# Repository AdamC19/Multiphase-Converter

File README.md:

# Multiphase Forward Converter
This repo contains the hardware source files for my digitally controlled multiphase isolated 1000W forward
converter. (firmware source code repo is
[here](https://github.com/AdamC19/Multiphase-Converter-FW).) This is a work in progress

## Update December 2020
First prototype has been built up, initial testing is promising! See more [here](http://acordingley.us/multiphase-converter/).

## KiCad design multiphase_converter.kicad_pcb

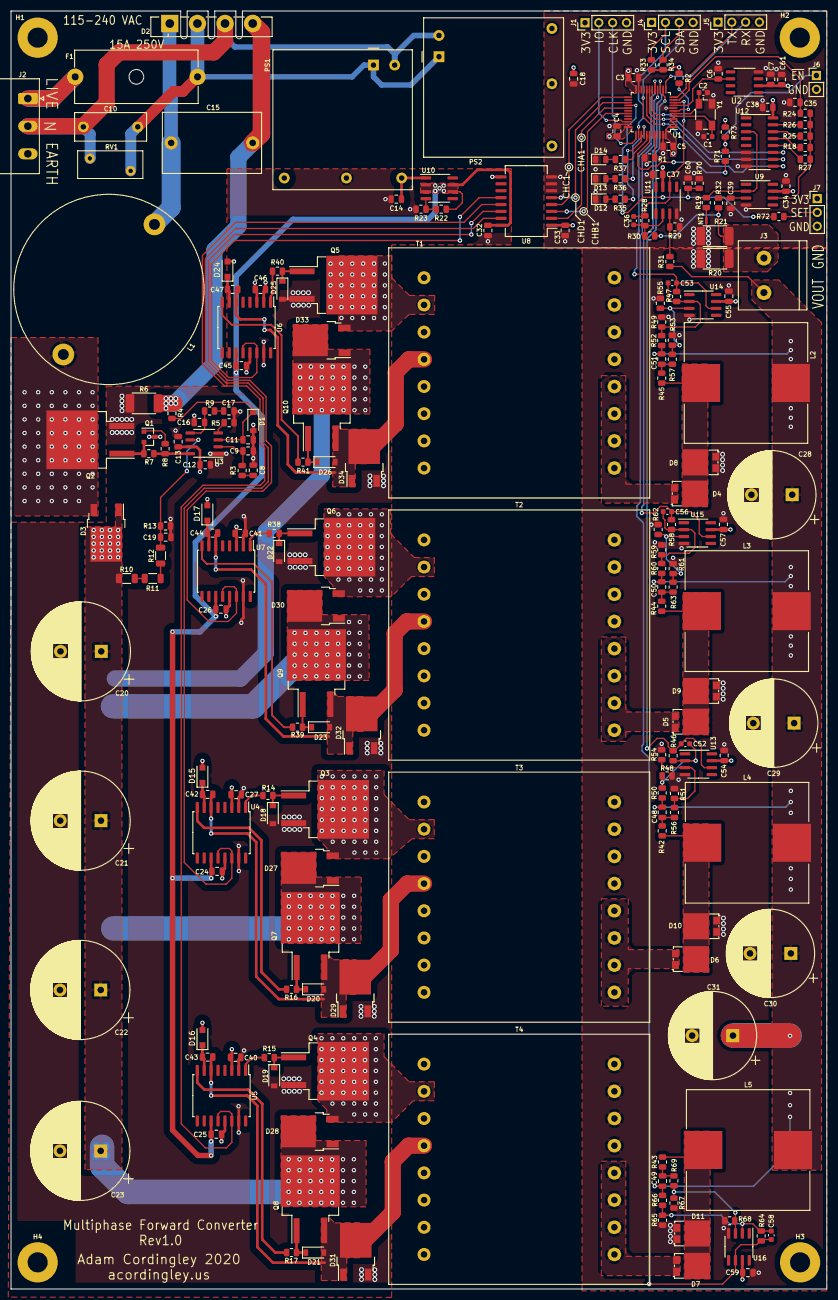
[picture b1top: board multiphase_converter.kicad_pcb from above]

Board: 4 copper layers, 150.0 x 235.0 mm, 220 parts (0 on the bottom side), 123 nets.

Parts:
C1, C2: 18p; C_0603_1608Metric
C3, C4, C5, C7, C13, C24, C25, C26, C27, C32, C33, C34, C35, C37, C38, C40, C41, C42, C43, C44, C45, C46, C47, C48, C49, C50, C51, C54, C55, C57, C59, C60: 0.1u; C_0805_2012Metric
C6, C12, C61: 1u; C_0805_2012Metric
C8: DNP; C_0805_2012Metric
C9, C11: 1200p; C_0805_2012Metric
C10: 4700p; C_Rect_L13.0mm_W5.0mm_P10.00mm_FKS3_FKP3_MKS4
C14, C18: 10u; C_0805_2012Metric
C15: R463I347050N0M; C_Rect_L18.0mm_W11.0mm_P15.00mm_FKS3_FKP3
C16: 2.2u; C_0805_2012Metric
C17: 22u; C_0805_2012Metric
C19: 680p; C_0805_2012Metric
C20, C21, C22, C23: 220u; CP_Radial_D18.0mm_P7.50mm
C28, C29, C30, C31: UCS2C221MHD1TN; CP_Radial_D16.0mm_P7.50mm
C36, C52, C53, C56, C58: 6.8p; C_0603_1608Metric
C39: 0.01u; C_0805_2012Metric
D1: 1N4148W; D_SOD-123
D2: GBU2510-G; Diode_Bridge_Vishay_GBU
D3, D27, D28, D29, D30, D31, D32, D33, D34: C3D04060E; TO-252-2
D4, D5, D6, D7, D8, D9, D10, D11: FSV15100V; TO-277A
D12, D13, D14: LED; LED_0805_2012Metric
D15, D16, D17, D24: S1MFL; D_SOD-123F
D18, D19, D20, D21, D22, D23, D25, D26: 15V; D_SOD-123
F1: 0031.8201; Fuseholder_Cylinder-5x20mm_Schurter_0031_8201_Horizontal_Op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
H1, H2, H3, H4: #6; MountingHole_3.7mm_Pad
J1, J4, J5: Conn_01x04_Male; PinHeader_1x04_P2.54mm_Vertical
J2: 1923872; PhoenixContact_MSTBA_2,5_3-G-5,08_1x03_P5.08mm_Horizontal
J3: 1714955; Phoenix_MKDS_5_2-6,35
J6: Conn_01x02_Male; PinHeader_1x02_P2.54mm_Vertical
J7: Conn_01x03_Male; PinHeader_1x03_P2.54mm_Vertical
L1: 120u; Bourns_1140_121K
L2, L3, L4, L5: 74435583300; L_Wuerth_HCI-2212
NT1: Net-Tie_2; NetTie-2_SMD_Pad0.5mm
PS1: RAC05-12SK; Converter_ACDC_RECOM_RAC05-xxSK_THT
PS2: RAC05-3.3SK; Converter_ACDC_RECOM_RAC05-xxSK_THT
Q1: BC807; SOT-23
Q2: IPB60R060P7ATMA1; TO-263-2
Q3, Q4, Q5, Q6, Q7, Q8, Q9, Q10: Q_NMOS_GDS; TO-263-2
R1, R2, R8, R19, R24, R32: 1k; R_0805_2012Metric
R3: DNP; R_0805_2012Metric
R4: 220; R_0805_2012Metric
R5: 13.7k; R_0805_2012Metric
R6: 0.015; R_2512_Power
R7, R14, R15, R16, R17, R38, R39, R40, R41: 3.3; R_0805_2012Metric
R9: 4.7k; R_0805_2012Metric
R10, R11, R12: 330k; R_1206_3216Metric
R13: 14.3k; R_0805_2012Metric
R18: 1.5M; R_0805_2012Metric
R20, R21: 0.003; R_2512_Power
R22: 240; R_0805_2012Metric
R23: 720; R_0805_2012Metric
R25, R30, R31, R50, R52, R56, R57, R60, R63, R66, R69, R70: 200k; R_0805_2012Metric
R26, R71, R72: 100k; R_0805_2012Metric
R27: 50k; R_0805_2012Metric
R28, R29, R48, R49, R51, R53, R59, R61, R65, R67, R73: 10k; R_0805_2012Metric
R33, R34: 2.2k; R_0805_2012Metric
R35, R36, R37: 330; R_0805_2012Metric
R42, R43, R44, R45: 25k; R_0805_2012Metric
R46, R47, R54, R55, R58, R62, R64, R68: 2.4M; R_0805_2012Metric
RV1: MOV-10D391KTR; RV_Disc_D12mm_W5.1mm_P7.5mm
T1, T2, T3, T4: Wurth_760895751
U1: STM32F334C8Tx; LQFP-48_7x7mm_P0.5mm
U2: ADR45xx; SO-8_3.9x4.9mm_P1.27mm
U3: UCC28180; SO-8_3.9x4.9mm_P1.27mm
U4, U5, U6, U7: IR2113S; SOIC-16W_7.5x10.3mm_P1.27mm
U8: ADuM260N; SOIC-16W_7.5x12.8mm_P1.27mm
U9: AD8551; SOIC-8_3.9x4.9mm_P1.27mm
U10: LM317L_SO8; SOIC-8_3.9x4.9mm_P1.27mm
U11, U13, U14, U15, U16: TSV911IDT; SOIC-8_3.9x4.9mm_P1.27mm
U12: 74HC4051; SOIC-16_3.9x9.9mm_P1.27mm
Y1: ABM3B-16.000MHZ-B2-T; Crystal_SMD_Abracon_ABM3B-4Pin_5.0x3.2mm

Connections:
+3V3: C3.2, C4.2, C5.2, C7.1, C18.1, C33.1, C34.1, C37.1, C38.1, C54.1, C55.1, C57.1, C59.1, C61.2, J1.1, J4.1, J5.1, J7.1, PS2.5, R2.1, R33.1, R34.1, R73.1, U1.1, U1.24, U1.36, U1.48, U2.2, U8.1, U9.7, U11.7, U12.16, U13.7, U14.7, U15.7, U16.7
+5VA: C24.1, C25.1, C26.1, C32.1, C45.1, R22.1, U4.11, U5.11, U6.11, U7.11, U8.16, U10.2, U10.3, U10.6, U10.7
+12V: C12.2, C13.2, C14.1, C27.2, C40.2, C41.2, C46.2, D15.2, D16.2, D17.2, D24.2, PS1.5, U3.7, U4.3, U5.3, U6.3, U7.3, U10.1
/Control/ENABLE: R71.2, U1.42
/Control/RX: J5.3, U1.13
/Control/SCL: J4.2, R33.2, U1.38
/Control/SDA: J4.3, R34.2, U1.43
/Control/SWDCLK: J1.3, U1.37
/Control/SWDIO: J1.2, U1.34
/Control/TX: J5.2, U1.12
/Control/VREF: C6.2, U1.9, U2.6
/Control/V_SET: C60.1, R70.2, R72.1, U1.28
/Converter Stage/P1_GATE: U4.12, U4.14, U8.15
/Converter Stage/P1_ISNS: C48.2, R42.1, R56.2
/Converter Stage/P2_GATE: U7.12, U7.14, U8.14
/Converter Stage/P2_ISNS: C50.2, R44.1, R63.2
/Converter Stage/P3_GATE: U5.12, U5.14, U8.13
/Converter Stage/P3_ISNS: C49.2, R43.1, R69.2
/Converter Stage/P4_GATE: U6.12, U6.14, U8.12
/Converter Stage/P4_ISNS: C51.2, R45.1, R57.2
/Converter Stage/T1_HI: C47.1, D26.2, D34.1, D34.2, Q10.3, T1.12, U6.6
/Converter Stage/T2_HI: C44.1, D23.2, D32.1, D32.2, Q9.3, T2.12, U7.6
/Converter Stage/T3_HI: C42.1, D20.2, D29.1, D29.2, Q7.3, T3.12, U4.6
/Converter Stage/T3_LO: D27.3, Q3.2, T3.10
/Converter Stage/T4_HI: C43.1, D21.2, D31.1, D31.2, Q8.3, T4.12, U5.6
/Converter Stage/VOUT_LO: J3.2, R20.1, R21.1, R30.2, R32.2
/Mains Power Input/LINE_IN: F1.2, J2.1
GNDA: C8.1, C9.1, C11.1, C12.1, C13.1, C14.2, C16.1, C17.1, C19.2, C20.2, C21.2, C22.2, C23.2, C24.2, C25.2, C26.2, C27.1, C32.2, C40.1, C41.1, C45.2, C46.1, D1.2, D18.2, D19.2, D22.2, D25.2, D29.3, D31.3, D32.3, D34.3, PS1.4, Q1.3, Q2.3, Q3.3, Q4.3, Q5.3, Q6.3, R5.1, R6.1, R13.1, R23.2, U3.1, U4.2, U4.13, U4.15, U5.2, U5.13, U5.15, U6.2, U6.13, U6.15, U7.2, U7.13, U7.15, U8.9
GNDD: C1.2, C2.2, C3.1, C4.1, C5.1, C6.1, C7.2, C18.2, C28.2, C29.2, C30.2, C31.2, C33.2, C34.2, C35.1, C37.2, C38.2, C39.1, C54.2, C55.2, C57.2, C59.2, C60.2, C61.1, D8.1, D8.2, D9.1, D9.2, D10.1, D10.2, D11.1, D11.2, D12.1, D13.1, D14.1, J1.4, J4.4, J5.4, J6.2, J7.3, NT1.2, PS2.4, R1.2, R20.2, R21.2, R29.1, R48.2, R49.2, R51.2, R53.2, R54.2, R55.2, R59.2, R61.2, R62.2, R65.2, R67.2, R68.2, R70.1, T1.5, T1.6, T1.7, T1.8, T2.5, T2.6, T2.7, T2.8, T3.5, T3.6, T3.7, T3.8, T4.5, T4.6, T4.7, T4.8, U1.8, U1.23, U1.35, U1.47, U2.4, U8.6, U8.7, U8.8, U9.4, U11.4, U12.6, U12.7, U12.8, U13.4, U14.4, U15.4, U16.4, Y1.2, Y1.4
HRTIM_CHA1: U1.29, U8.2
HRTIM_CHB1: U1.31, U8.3
HRTIM_CHC1: U1.25, U8.4
HRTIM_CHD1: U1.27, U8.5
IMUX_0: U1.18, U12.11
IMUX_1: U1.19, U12.10
IMUX_2: U1.20, U12.9
I_FB: C35.2, R24.1, U1.11
LINE: C10.1, D2.2, F1.1, PS1.1, PS2.1, RV1.1
NEUT: C10.2, D2.3, J2.2, PS1.2, PS2.2, RV1.2
unnamed: C1.1, U1.5, Y1.3
unnamed: C2.1, U1.6, Y1.1
unnamed: C8.2, R3.1
unnamed: C9.2, R3.2, U3.2
unnamed: C11.2, D1.1, R4.1, U3.3
unnamed: C15.1, D2.1, L1.1
unnamed: C15.2, D2.4, R4.2, R6.2
unnamed: C16.2, R9.1, U3.5
unnamed: C17.2, R9.2
unnamed: C19.1, R12.1, R13.2, U3.6
unnamed: C36.2, R28.1, R30.1, U11.2
unnamed: C39.2, R32.1, U9.3
unnamed: C42.2, D15.1, U4.7
unnamed: C43.2, D16.1, U5.7
unnamed: C44.2, D17.1, U7.7
unnamed: C47.2, D24.1, U6.7
unnamed: C52.2, R46.1, R48.1, R50.1, U13.2
unnamed: C53.2, R47.1, R49.1, R52.1, U14.2
unnamed: C56.2, R58.1, R59.1, R60.1, U15.2
unnamed: C58.2, R64.1, R65.1, R66.1, U16.2
unnamed: D3.3, L1.2, Q2.2
unnamed: D4.1, D4.2, T1.1, T1.2, T1.3, T1.4
unnamed: D4.3, D8.3, L2.1, R45.2
unnamed: D5.1, D5.2, T2.1, T2.2, T2.3, T2.4
unnamed: D5.3, D9.3, L3.1, R44.2
unnamed: D6.1, D6.2, T3.1, T3.2, T3.3, T3.4
unnamed: D7.1, D7.2, T4.1, T4.2, T4.3, T4.4
unnamed: D6.3, D10.3, L4.1, R42.2
unnamed: D7.3, D11.3, L5.1, R43.2
unnamed: D12.2, R35.2
unnamed: D13.2, R36.2
unnamed: D14.2, R37.2
unnamed: D18.1, Q3.1, R14.2
unnamed: D19.1, Q4.1, R15.2
unnamed: D20.1, Q7.1, R16.2
unnamed: D21.1, Q8.1, R17.2
unnamed: D22.1, Q6.1, R38.2
unnamed: D23.1, Q9.1, R39.2
unnamed: D25.1, Q5.1, R40.2
unnamed: D26.1, Q10.1, R41.2
unnamed: D28.3, Q4.2, T4.10
unnamed: D30.3, Q6.2, T2.10
unnamed: D33.3, Q5.2, T1.10
unnamed: J6.1, R71.1, R73.2
unnamed: J7.2, R72.2
unnamed: NT1.1, R19.2
unnamed: Q1.1, R8.1
unnamed: Q1.2, Q2.1, R7.1
unnamed: R1.1, U1.44
unnamed: R2.2, U1.7
unnamed: R5.2, U3.4
unnamed: R7.2, R8.2, U3.8
unnamed: R10.1, R11.2
unnamed: R11.1, R12.2
unnamed: R14.1, U4.1
unnamed: R15.1, U5.1
unnamed: R16.1, U4.8
unnamed: R17.1, U5.8
unnamed: R18.1, R24.2, R25.1, R26.1, R27.1, U9.6
unnamed: R18.2, U12.13
unnamed: R19.1, U9.2, U12.3
unnamed: R22.2, R23.1, U10.4
unnamed: R25.2, U12.14
unnamed: R26.2, U12.15
unnamed: R27.2, U12.12
unnamed: R29.2, R31.1, U11.3
unnamed: R35.1, U1.39
unnamed: R36.1, U1.40
unnamed: R37.1, U1.41
unnamed: R38.1, U7.1
unnamed: R39.1, U7.8
unnamed: R40.1, U6.1
unnamed: R41.1, U6.8
unnamed: R51.1, R54.1, R56.1, U13.3
unnamed: R53.1, R55.1, R57.1, U14.3
unnamed: R61.1, R62.1, R63.1, U15.3
unnamed: R67.1, R68.1, R69.1, U16.3
P1_IFB: C52.1, R46.2, U1.14, U13.6
P2_IFB: C56.1, R58.2, U1.15, U15.6
P3_IFB: C58.1, R64.2, U1.16, U16.6
P4_IFB: C53.1, R47.2, U1.17, U14.6
VBUS: C20.1, C21.1, C22.1, C23.1, D3.1, D3.2, D27.1, D27.2, D28.1, D28.2, D30.1, D30.2, D33.1, D33.2, Q7.2, Q8.2, Q9.2, Q10.2, R10.2
VCC: C28.1, C29.1, C30.1, C31.1, C48.1, C49.1, C50.1, C51.1, J3.1, L2.2, L3.2, L4.2, L5.2, R31.2, R50.2, R52.2, R60.2, R66.2
V_FB: C36.1, R28.2, U1.10, U11.6

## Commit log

2020-11-15 All work to date
2020-11-15 Add link to firmware repo in README
2020-11-16 Updates to PCB to get ready for manufacture
2020-11-18 Final design sent out for fabrication
2020-12-09 Updates to README
2020-12-13 Annotations to schematics, fix bootstrap diodes
